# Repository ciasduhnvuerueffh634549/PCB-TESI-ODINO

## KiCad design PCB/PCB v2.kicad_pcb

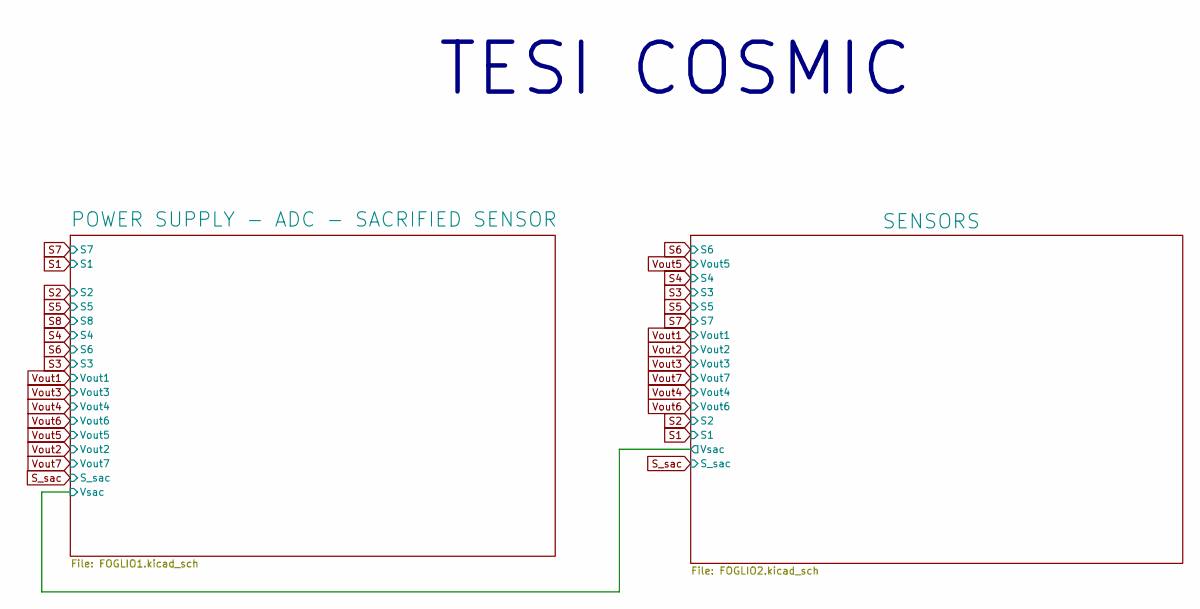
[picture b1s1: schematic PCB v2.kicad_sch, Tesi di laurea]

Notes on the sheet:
TESI COSMIC

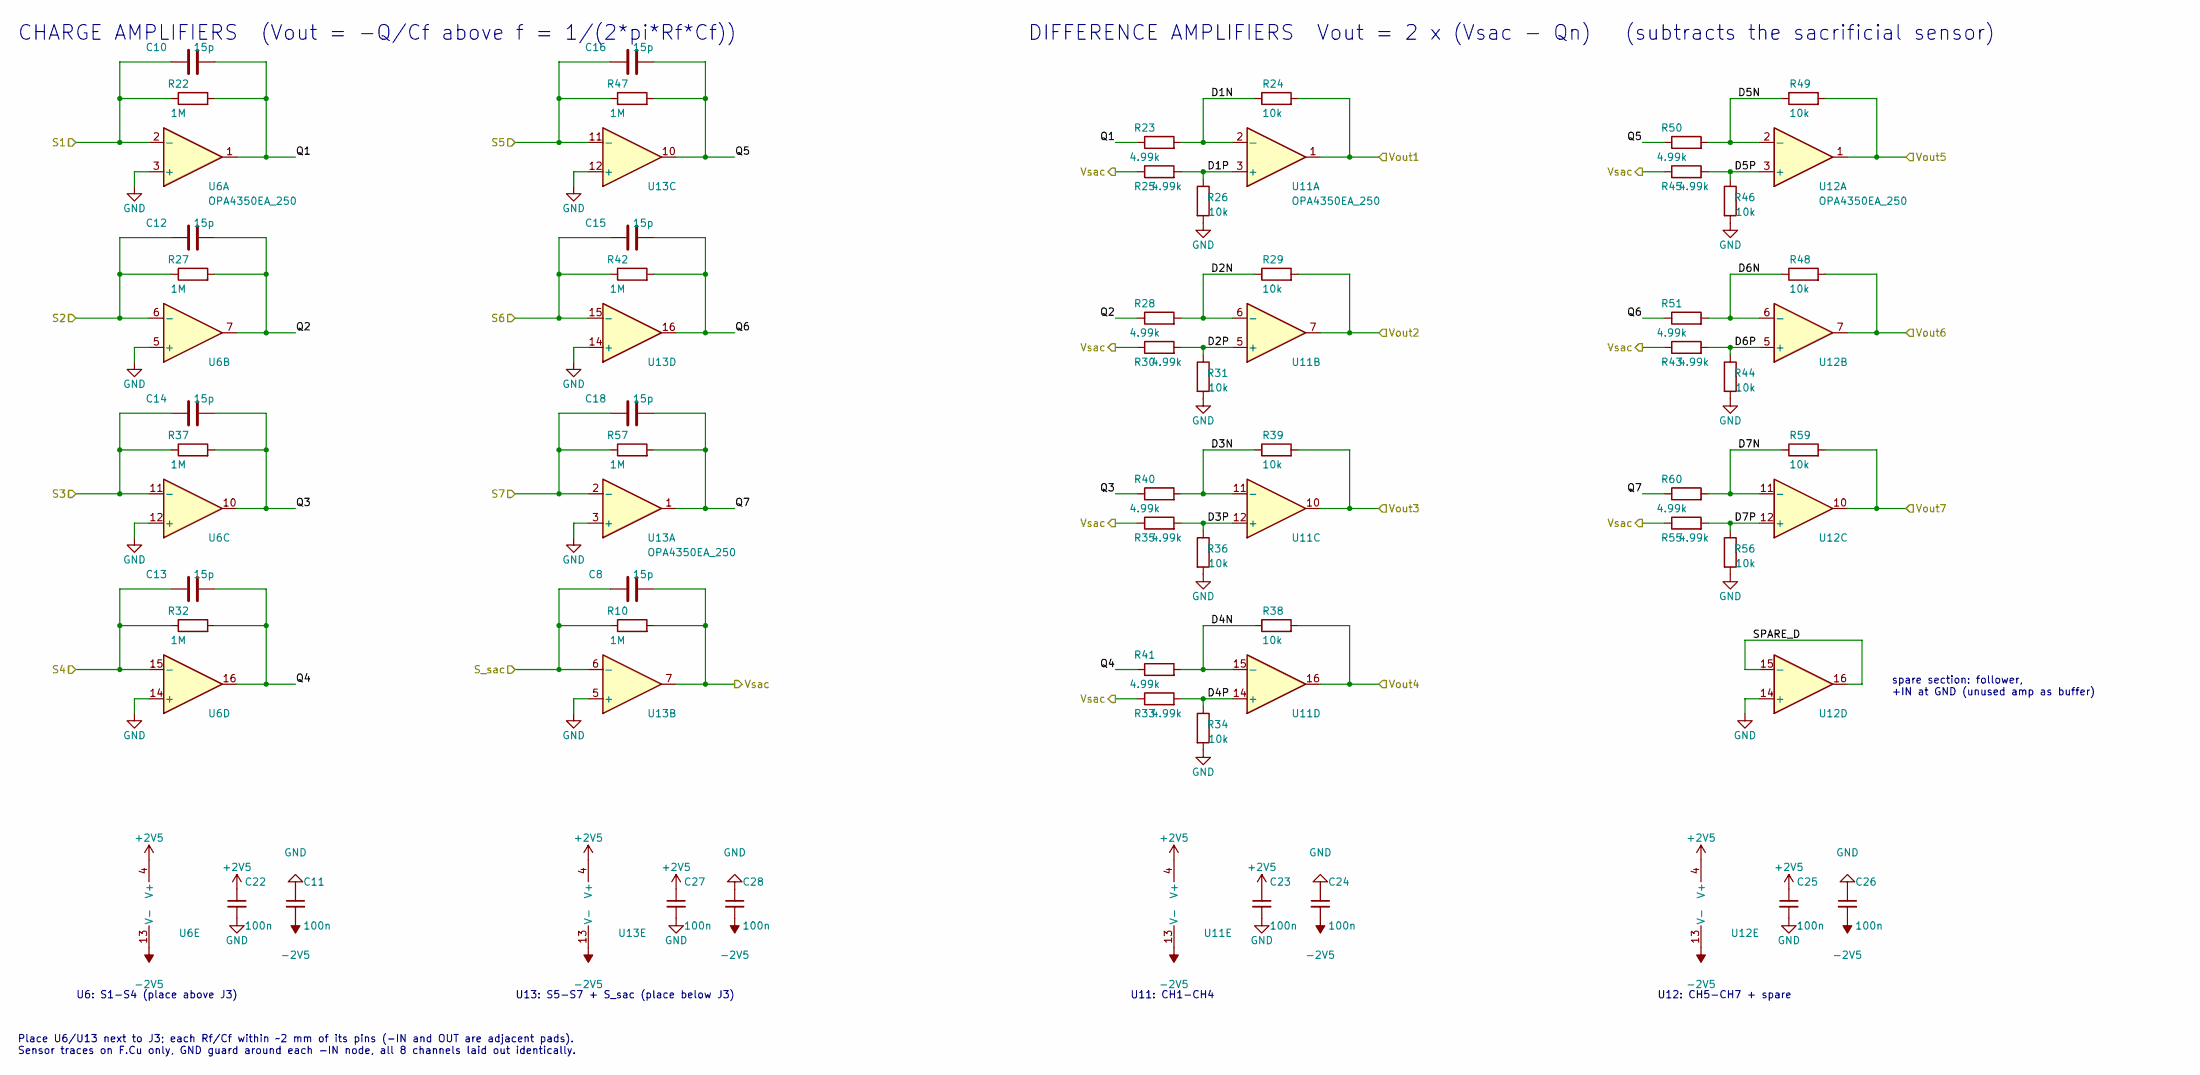
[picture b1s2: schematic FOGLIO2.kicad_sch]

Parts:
C8, C10, C12, C13, C14, C15, C16, C18: 15p; C_0603_1608Metric; MPN CL10C150JB8NNNC
C11, C22, C23, C24, C25, C26, C27, C28: 100n; C_0603_1608Metric; MPN GRM188R72A104KA35D
R10, R22, R27, R32, R37, R42, R47, R57: 1M; R_0603_1608Metric; MPN RN73R1JTTD1004B25
R23, R25, R28, R30, R33, R35, R40, R41, R43, R45, R50, R51, R55, R60: 4.99k; R_0603_1608Metric; MPN RT0603BRD074K99L
R24, R26, R29, R31, R34, R36, R38, R39, R44, R46, R48, R49, R56, R59: 10k; R_0603_1608Metric; MPN RT0603BRD0710KL
U6, U11, U12, U13: OPA4350EA_250; SOP63P600X175-16N; MPN OPA4350EA/250

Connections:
+2V5: C22.1, C23.1, C25.1, C27.1, U6.4 (V+), U11.4 (V+), U12.4 (V+), U13.4 (V+); also elsewhere on the board
-2V5: C11.2, C24.2, C26.2, C28.2, U6.13 (V-), U11.13 (V-), U12.13 (V-), U13.13 (V-); also elsewhere on the board
/POWER SUPPLY - ADC - SACRIFIED SENSOR/Vsac: C8.2, R10.2, R25.1, R30.1, R33.1, R35.1, R43.1, R45.1, R55.1, U13.7; also elsewhere on the board
/SENSORS/D1N: R23.2, R24.1, U11.2 (-)
/SENSORS/D1P: R25.2, R26.1, U11.3 (+)
/SENSORS/D2N: R28.2, R29.1, U11.6 (-)
/SENSORS/D2P: R30.2, R31.1, U11.5 (+)
/SENSORS/D3N: R39.1, R40.2, U11.11 (-)
/SENSORS/D3P: R35.2, R36.1, U11.12 (+)
/SENSORS/D4N: R38.1, R41.2, U11.15 (-)
/SENSORS/D4P: R33.2, R34.1, U11.14 (+)
/SENSORS/D5N: R49.1, R50.2, U12.2 (-)
/SENSORS/D5P: R45.2, R46.1, U12.3 (+)
/SENSORS/D6N: R48.1, R51.2, U12.6 (-)
/SENSORS/D6P: R43.2, R44.1, U12.5 (+)
/SENSORS/D7N: R59.1, R60.2, U12.11 (-)
/SENSORS/D7P: R55.2, R56.1, U12.12 (+)
/SENSORS/Q1: C10.2, R22.2, R23.1, U6.1
/SENSORS/Q2: C12.2, R27.2, R28.1, U6.7
/SENSORS/Q3: C14.2, R37.2, R40.1, U6.10
/SENSORS/Q4: C13.2, R32.2, R41.1, U6.16
/SENSORS/Q5: C16.2, R47.2, R50.1, U13.10
/SENSORS/Q6: C15.2, R42.2, R51.1, U13.16
/SENSORS/Q7: C18.2, R57.2, R60.1, U13.1
/SENSORS/SPARE_D: U12.15 (-), U12.16
GND: C11.1, C22.2, C23.2, C24.1, C25.2, C26.1, C27.2, C28.1, R26.2, R31.2, R34.2, R36.2, R44.2, R46.2, R56.2, U6.3 (+), U6.5 (+), U6.12 (+), U6.14 (+), U12.14 (+), U13.3 (+), U13.5 (+), U13.12 (+), U13.14 (+); also elsewhere on the board
S1: C10.1, R22.1, U6.2 (-); also elsewhere on the board
S2: C12.1, R27.1, U6.6 (-); also elsewhere on the board
S3: C14.1, R37.1, U6.11 (-); also elsewhere on the board
S4: C13.1, R32.1, U6.15 (-); also elsewhere on the board
S5: C16.1, R47.1, U13.11 (-); also elsewhere on the board
S6: C15.1, R42.1, U13.15 (-); also elsewhere on the board
S7: C18.1, R57.1, U13.2 (-); also elsewhere on the board
S_sac: C8.1, R10.1, U13.6 (-); also elsewhere on the board
Vout1: R24.2, U11.1; also elsewhere on the board
Vout2: R29.2, U11.7; also elsewhere on the board
Vout3: R39.2, U11.10; also elsewhere on the board
Vout4: R38.2, U11.16; also elsewhere on the board
Vout5: R49.2, U12.1; also elsewhere on the board
Vout6: R48.2, U12.7; also elsewhere on the board
Vout7: R59.2, U12.10; also elsewhere on the board

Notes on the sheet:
Place U6/U13 next to J3; each Rf/Cf within ~2 mm of its pins (-IN and OUT are adjacent pads). Sensor traces on F.Cu only, GND guard around each -IN node, all 8 channels laid out identically.
U12: CH5-CH7 + spare
U13: S5-S7 + S_sac (place below J3)
CHARGE AMPLIFIERS (Vout = -Q/Cf above f = 1/(2*pi*Rf*Cf))
spare section: follower, +IN at GND (unused amp as buffer)
U6: S1-S4 (place above J3)
U11: CH1-CH4
DIFFERENCE AMPLIFIERS Vout = 2 x (Vsac - Qn) (subtracts the sacrificial sensor)

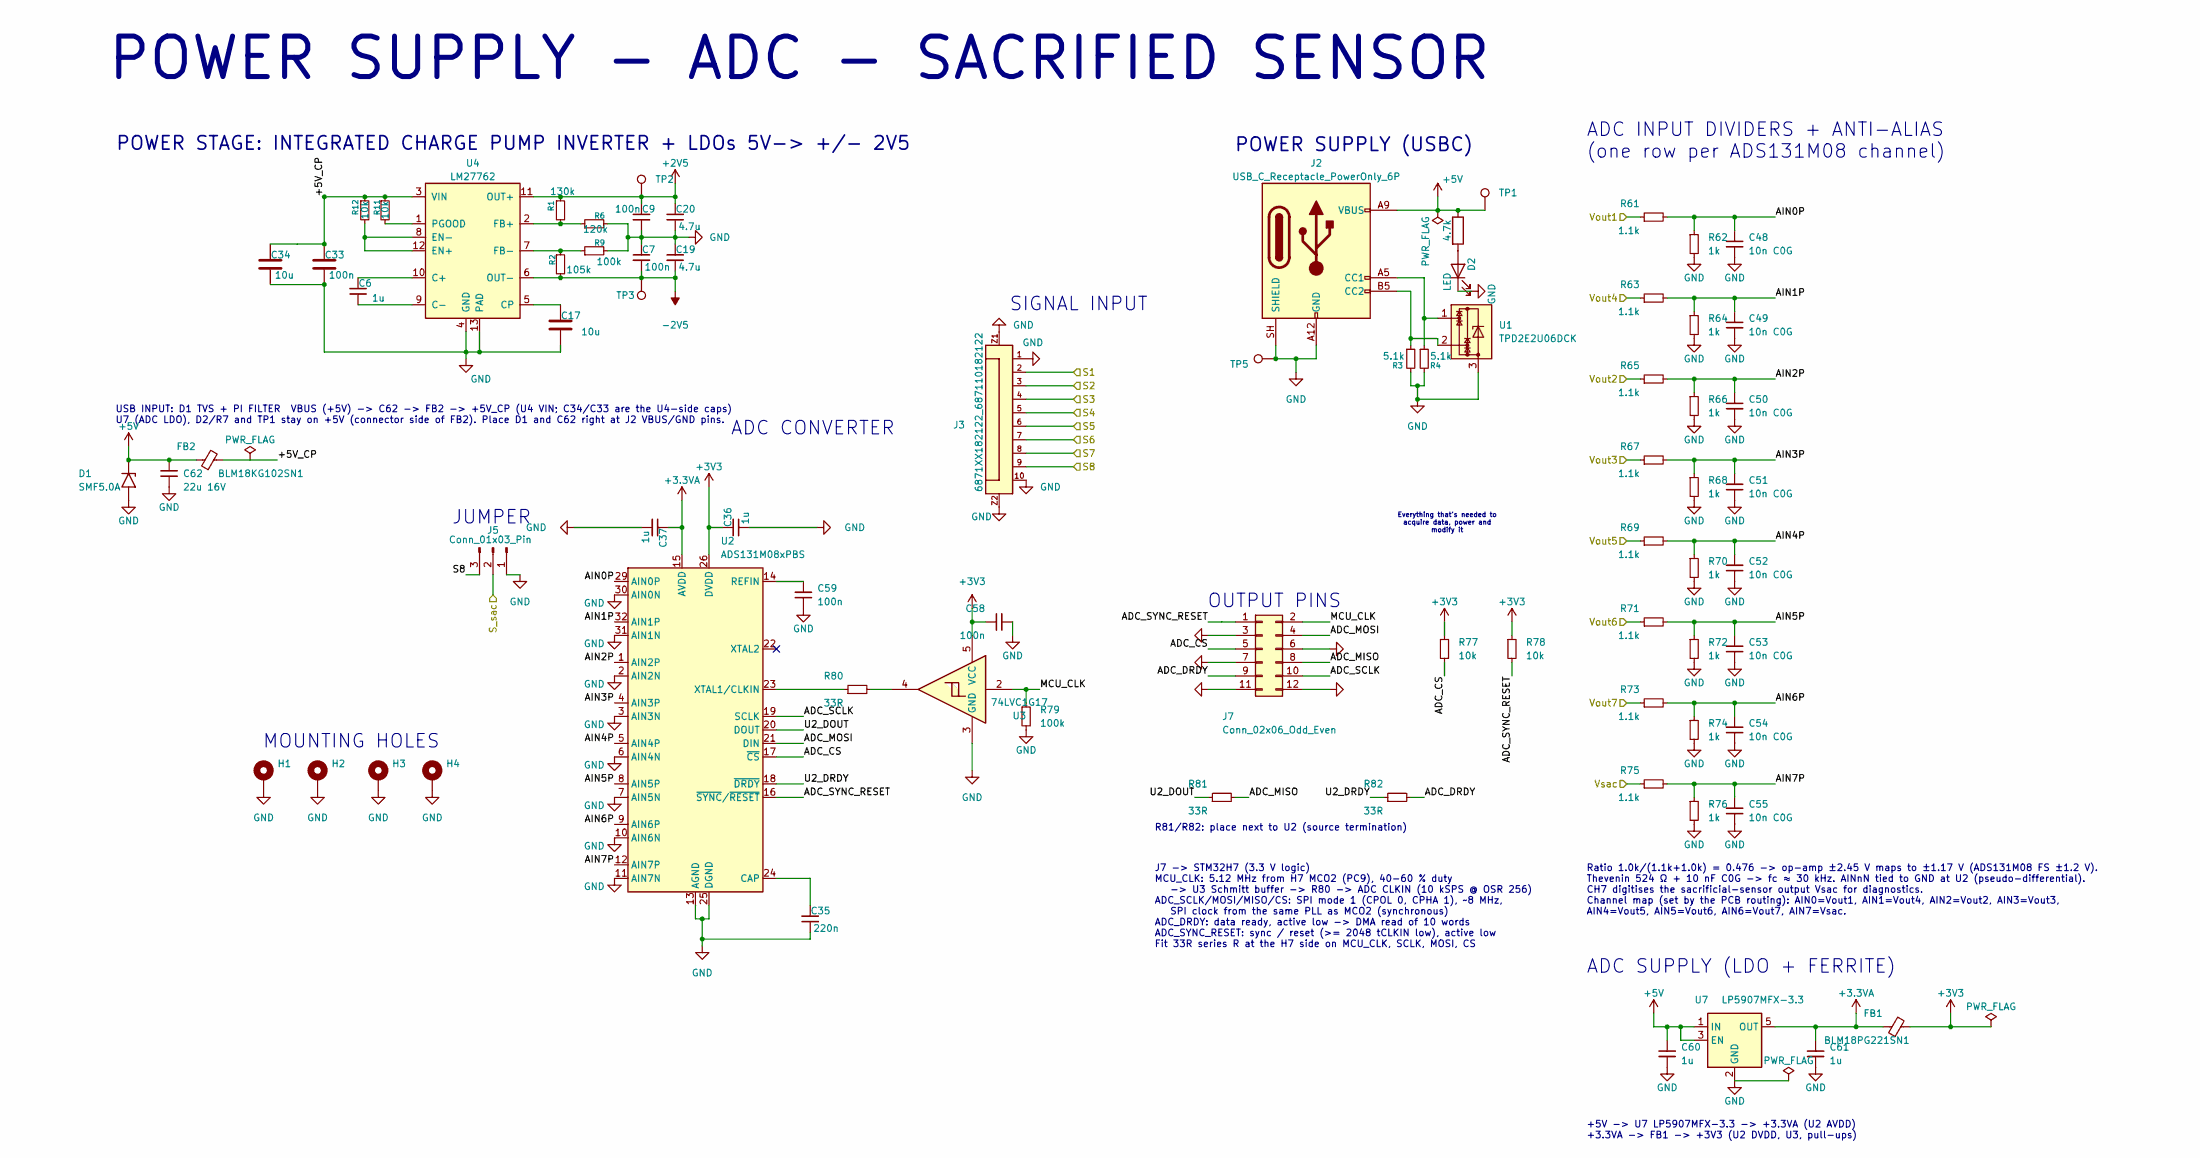
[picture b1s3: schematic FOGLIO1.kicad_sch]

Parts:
C6, C36, C37, C60, C61: 1u; C_0603_1608Metric; MPN GRT188R71E105KE13D
C7, C9, C33, C58, C59: 100n; C_0603_1608Metric; MPN GRM188R72A104KA35D
C17, C34: 10u; C_0805_2012Metric; MPN GRJ21BR61E106KE01L
C19, C20: 4.7u; C_0603_1608Metric; MPN GRT188R61C475KE13D
C35: 220n; C_0603_1608Metric; MPN GRM188R71E224KA88D
C48, C49, C50, C51, C52, C53, C54, C55: 10n C0G; C_0603_1608Metric; MPN GRM1885C1H103JA01D
C62: 22u 16V; C_0805_2012Metric; MPN GRM219R61C226ME15K
D1: SMF5.0A; D_SMF; MPN SMF5.0A
D2: LED; LED_0603_1608Metric; MPN 150060GS75000
FB1: BLM18PG221SN1; L_0603_1608Metric; MPN BLM18PG221SN1D
FB2: BLM18KG102SN1; L_0603_1608Metric; MPN BLM18KG102SN1D
H1, H2, H3, H4: MountingHole_Pad; MountingHole_2.2mm_M2_DIN965_Pad
J2: USB_C_Receptacle_PowerOnly_6P; USB_C_Receptacle_GCT_USB4125-xx-x_6P_TopMnt_Horizontal; MPN USB4125-GF-A
J3: 6871XX182122_687110182122; 687110182122; MPN 687110182122
J5: Conn_01x03_Pin; PinHeader_1x03_P1.27mm_Vertical_SMD_Pin1Right; MPN M50-3630342
J7: Conn_02x06_Odd_Even; PinHeader_2x06_P2.54mm_Vertical_SMD; MPN 61001221121
R1: 130k; R_0603_1608Metric; MPN RC0603FR-07130KL
R2: 105k; R_0603_1608Metric; MPN AC0603FR-07105KL
R3, R4: 5.1k; R_0603_1608Metric; MPN RC0603FR-075K1L
R6: 120k; R_0603_1608Metric; MPN RC0603FR-07120KL
R7: 4.7k; R_0603_1608Metric; MPN RC0603FR-074K7L
R9, R79: 100k; R_0603_1608Metric; MPN RC0603FR-07100KL
R11, R12, R77, R78: 10k; R_0603_1608Metric; MPN RC0603FR-0710KL
R61, R63, R65, R67, R69, R71, R73, R75: 1.1k; R_0603_1608Metric; MPN RT0603BRD071K1L
R62, R64, R66, R68, R70, R72, R74, R76: 1k; R_0603_1608Metric; MPN RN73R1JTTD1001B25
R80, R81, R82: 33R; R_0603_1608Metric; MPN RC0603FR-0733RL
TP1, TP2, TP3, TP5: TestPoint; TestPoint_Pad_D1.5mm
U1: TPD2E2U06DCK; SOT-323_SC-70; MPN TPD2E2U06DCKR
U2: ADS131M08xPBS; TQFP-32_5x5mm_P0.5mm; MPN ADS131M08IPBSR
U3: 74LVC1G17; SOT-23-5; MPN SN74LVC1G17DBVR
U4: LM27762; WSON-12-1EP_3x2mm_P0.5mm_EP1x2.65_ThermalVias; MPN LM27762DSSR
U7: LP5907MFX-3.3; SOT-23-5; MPN LP5907MFX-3.3/NOPB

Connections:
+2V5: C9.1, C20.1, R1.1, TP2.1 (1_1), U4.11 (OUT+); also elsewhere on the board
+3.3VA: C37.1, C61.1, FB1.1, U2.15 (AVDD), U7.5 (OUT)
+3V3: C36.1, C58.1, FB1.2, R77.1, R78.1, U2.26 (DVDD), U3.5 (VCC)
+5V: C60.1, C62.1, D1.1 (A1), FB2.1, J2.A9 (VBUS), J2.B9 (VBUS), R7.1, TP1.1 (1_1), U7.1 (IN), U7.3 (EN)
-2V5: C7.2, C19.2, R2.2, TP3.1 (1_1), U4.6 (OUT-); also elsewhere on the board
/POWER SUPPLY - ADC - SACRIFIED SENSOR/+5V_CP: C33.1, C34.1, FB2.2, R11.1, R12.1, U4.3 (VIN)
/POWER SUPPLY - ADC - SACRIFIED SENSOR/ADC_CS: J7.5, R77.2, U2.17 (~CS)
/POWER SUPPLY - ADC - SACRIFIED SENSOR/ADC_DRDY: J7.9, R82.2
/POWER SUPPLY - ADC - SACRIFIED SENSOR/ADC_MISO: J7.8, R81.2
/POWER SUPPLY - ADC - SACRIFIED SENSOR/ADC_MOSI: J7.4, U2.21 (DIN)
/POWER SUPPLY - ADC - SACRIFIED SENSOR/ADC_SCLK: J7.10, U2.19 (SCLK)
/POWER SUPPLY - ADC - SACRIFIED SENSOR/ADC_SYNC_RESET: J7.1, R78.2, U2.16 (~SYNC/~RESET)
/POWER SUPPLY - ADC - SACRIFIED SENSOR/AIN0P: C48.1, R61.2, R62.1, U2.29 (AIN0P)
/POWER SUPPLY - ADC - SACRIFIED SENSOR/AIN1P: C49.1, R63.2, R64.1, U2.32 (AIN1P)
/POWER SUPPLY - ADC - SACRIFIED SENSOR/AIN2P: C50.1, R65.2, R66.1, U2.1 (AIN2P)
/POWER SUPPLY - ADC - SACRIFIED SENSOR/AIN3P: C51.1, R67.2, R68.1, U2.4 (AIN3P)
/POWER SUPPLY - ADC - SACRIFIED SENSOR/AIN4P: C52.1, R69.2, R70.1, U2.5 (AIN4P)
/POWER SUPPLY - ADC - SACRIFIED SENSOR/AIN5P: C53.1, R71.2, R72.1, U2.8 (AIN5P)
/POWER SUPPLY - ADC - SACRIFIED SENSOR/AIN6P: C54.1, R73.2, R74.1, U2.9 (AIN6P)
/POWER SUPPLY - ADC - SACRIFIED SENSOR/AIN7P: C55.1, R75.2, R76.1, U2.12 (AIN7P)
/POWER SUPPLY - ADC - SACRIFIED SENSOR/MCU_CLK: J7.2, R79.1, U3.2
/POWER SUPPLY - ADC - SACRIFIED SENSOR/U2_DOUT: R81.1, U2.20 (DOUT)
/POWER SUPPLY - ADC - SACRIFIED SENSOR/U2_DRDY: R82.1, U2.18 (~DRDY)
/POWER SUPPLY - ADC - SACRIFIED SENSOR/Vsac: R75.1; also elsewhere on the board
GND: C7.1, C9.2, C17.2, C19.1, C20.2, C33.2, C34.2, C35.2, C36.2, C37.2, C48.2, C49.2, C50.2, C51.2, C52.2, C53.2, C54.2, C55.2, C58.2, C59.2, C60.2, C61.2, C62.2, D1.2 (A2), D2.1 (K), H1.1 (1_1), H2.1 (1_1), H3.1 (1_1), H4.1 (1_1), J2.A12 (GND), J2.B12 (GND), J2.SH (SHIELD), J3.1, J3.10, J3.Z1, J3.Z2, J5.1, J7.3, J7.6, J7.7, J7.11, J7.12, R3.2, R4.2, R6.2, R9.2, R62.2, R64.2, R66.2, R68.2, R70.2, R72.2, R74.2, R76.2, R79.2, TP5.1 (1_1), U1.3, U2.2 (AIN2N), U2.3 (AIN3N), U2.6 (AIN4N), U2.7 (AIN5N), U2.10 (AIN6N), U2.11 (AIN7N), U2.13 (AGND), U2.25 (DGND), U2.27 (AGND), U2.28 (AGND), U2.30 (AIN0N), U2.31 (AIN1N), U3.3 (GND), U4.4 (GND), U4.13 (PAD), U7.2 (GND); also elsewhere on the board
unnamed: D2.2 (A), R7.2
unnamed: J2.A5 (CC1), R4.1, U1.1
unnamed: J2.B5 (CC2), R3.1, U1.2
unnamed: R80.2, U3.4
unnamed: C35.1, U2.24 (CAP)
unnamed: C59.1, U2.14 (REFIN)
unnamed: R80.1, U2.23 (XTAL1/CLKIN)
unnamed: C6.1, U4.10 (C+)
unnamed: C6.2, U4.9 (C-)
unnamed: C17.1, U4.5 (CP)
unnamed: R12.2, U4.8 (EN-), U4.12 (EN+)
unnamed: R1.2, R6.1, U4.2 (FB+)
unnamed: R2.1, R9.1, U4.7 (FB-)
unnamed: R11.2, U4.1 (PGOOD)
S1: J3.2; also elsewhere on the board
S2: J3.3; also elsewhere on the board
S3: J3.4; also elsewhere on the board
S4: J3.5; also elsewhere on the board
S5: J3.6; also elsewhere on the board
S6: J3.7; also elsewhere on the board
S7: J3.8; also elsewhere on the board
S8: J3.9, J5.3
S_sac: J5.2; also elsewhere on the board
Vout1: R61.1; also elsewhere on the board
Vout2: R65.1; also elsewhere on the board
Vout3: R67.1; also elsewhere on the board
Vout4: R63.1; also elsewhere on the board
Vout5: R69.1; also elsewhere on the board
Vout6: R71.1; also elsewhere on the board
Vout7: R73.1; also elsewhere on the board

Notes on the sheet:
SIGNAL INPUT
MOUNTING HOLES
POWER STAGE: INTEGRATED CHARGE PUMP INVERTER + LDOs 5V-> +/- 2V5
ADC INPUT DIVIDERS + ANTI-ALIAS (one row per ADS131M08 channel)
ADC CONVERTER
ADC SUPPLY (LDO + FERRITE)
J7 -> STM32H7 (3.3 V logic) MCU_CLK: 5.12 MHz from H7 MCO2 (PC9), 40-60 % duty -> U3 Schmitt buffer -> R80 -> ADC CLKIN (10 kSPS @ OSR 256) ADC_SCLK/MOSI/MISO/CS: SPI mode 1 (CPOL 0, CPHA 1), ~8 MHz, SPI clock from the same PLL as MCO2 (synchronous) ADC_DRDY: data ready, active low -> DMA read of 1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
R81/R82: place next to U2 (source termination)
Ratio 1.0k/(1.1k+1.0k) = 0.476 -> op-amp ±2.45 V maps to ±1.17 V (ADS131M08 FS ±1.2 V). Thevenin 524 Ω + 10 nF C0G -> fc ≈ 30 kHz. AINnN tied to GND at U2 (pseudo-differential). CH7 digitises the sacrificial-sensor output Vsac for diagnostics. Channel map (set by the PCB routing): AIN0=Vout1, AIN1=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
Everything that's needed to acquire data, power and modify it
POWER SUPPLY (USBC)
POWER SUPPLY - ADC - SACRIFIED SENSOR
OUTPUT PINS
JUMPER
+5V -> U7 LP5907MFX-3.3 -> +3.3VA (U2 AVDD) +3.3VA -> FB1 -> +3V3 (U2 DVDD, U3, pull-ups)
USB INPUT: D1 TVS + PI FILTER VBUS (+5V) -> C62 -> FB2 -> +5V_CP (U4 VIN; C34/C33 are the U4-side caps) U7 (ADC LDO), D2/R7 and TP1 stay on +5V (connector side of FB2). Place D1 and C62 right at J2 VBUS/GND pins.

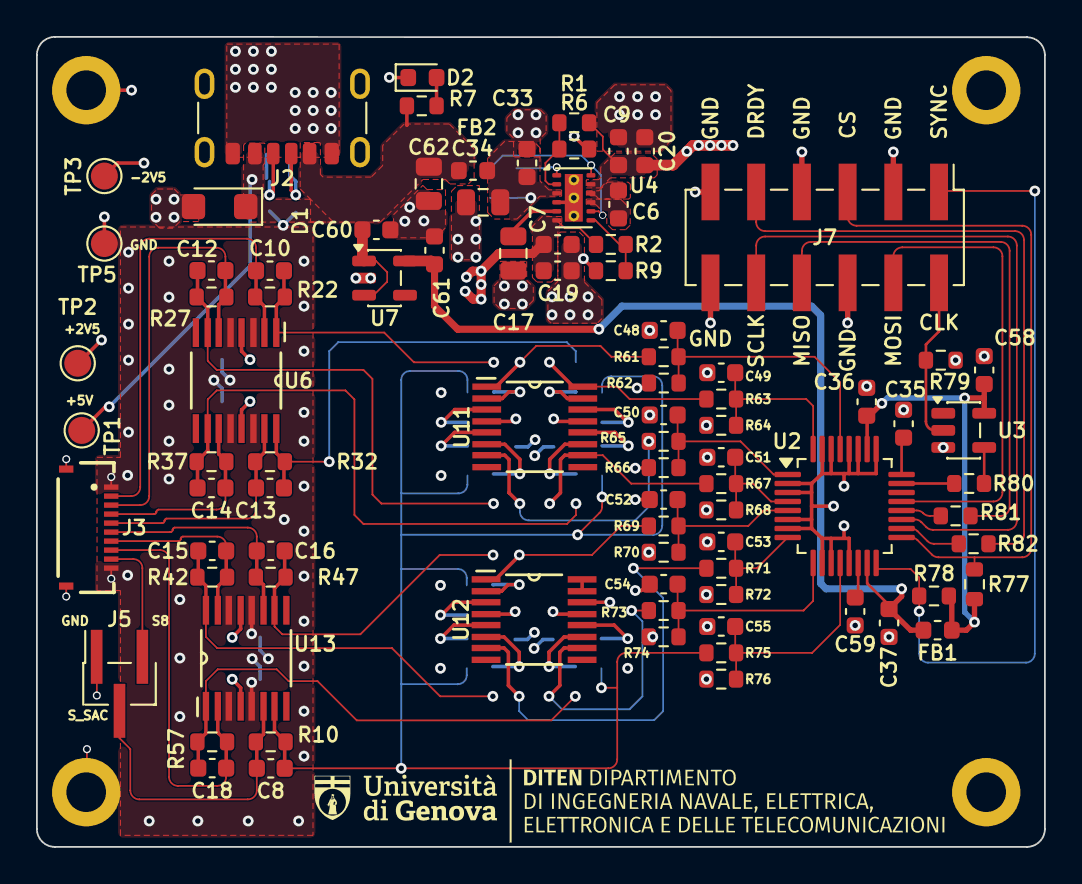
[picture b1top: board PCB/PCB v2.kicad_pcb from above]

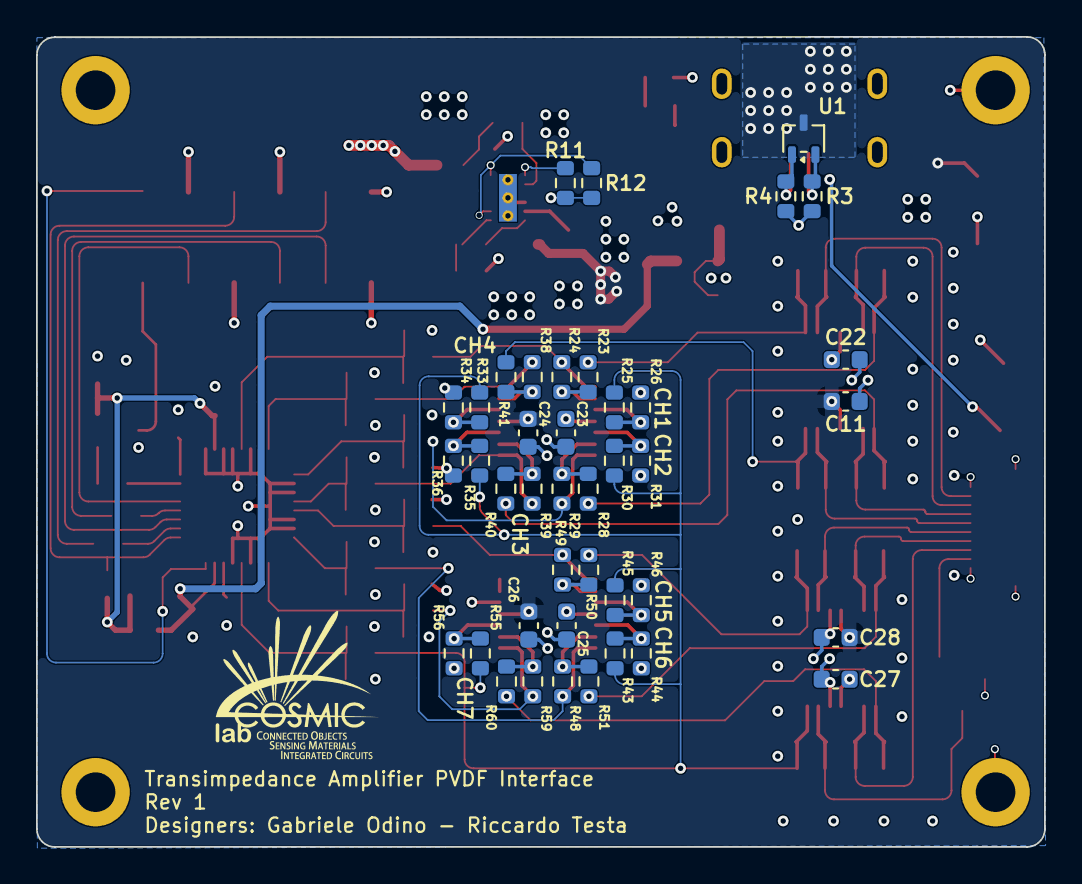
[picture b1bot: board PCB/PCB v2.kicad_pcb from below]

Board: 4 copper layers, 56.0 x 45.0 mm, 132 parts (41 on the bottom side), 77 nets.

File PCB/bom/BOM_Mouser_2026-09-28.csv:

Qty per board,References,Value,Description,Manufacturer,MPN,Mouser link,Mouser stock (2026-09-28),EUR/pc @10,EUR/pc @100,Footprint,Notes
5,"C6,C36,C37,C60,C61",1u,1 µF 25V X7R 0603,Murata,GRT188R71E105KE13D,https://www.mouser.it/c/?q=GRT188R71E105KE13D,"140,413",0.046,0.040,Capacitor_SMD:C_0603_1608Metric,
13,"C7,C9,C11,C22,C23,C24,C25,C26,C27,C28,C33,C58,C59",100n,100 nF 100V X7R 0603,Murata,GRM188R72A104KA35D,https://www.mouser.it/c/?q=GRM188R72A104KA35D,"1,304,093",0.075,0.046,Capacitor_SMD:C_0603_1608Metric,Replaces obsolete GRM188R71H104KA93D
8,"C8,C10,C12,C13,C14,C15,C16,C18",15p,15 pF 50V C0G ±5% 0603,Samsung Electro-Mechanics,CL10C150JB8NNNC,https://www.mouser.it/c/?q=CL10C150JB8NNNC,"53,656",0.039,0.023,Capacitor_SMD:C_0603_1608Metric,Rf||Cf; Murata 0603 15p C0G all NRND
2,"C17,C34",10u,10 µF 25V X5R 0805 soft term.,Murata,GRJ21BR61E106KE01L,https://www.mouser.it/c/?q=GRJ21BR61E106KE01L,"21,004",0.064,0.056,Capacitor_SMD:C_0805_2012Metric,C17 at about -5V; check DC bias
2,"C19,C20",4.7u,4.7 µF 16V X5R 0603,Murata,GRT188R61C475KE13D,https://www.mouser.it/c/?q=GRT188R61C475KE13D,"7,003",0.068,0.059,Capacitor_SMD:C_0603_1608Metric,±2V5 LDO outputs; check DC bias
1,C35,220n,220 nF 25V X7R 0603,Murata,GRM188R71E224KA88D,https://www.mouser.it/c/?q=GRM188R71E224KA88D,"9,632",0.043,0.026,Capacitor_SMD:C_0603_1608Metric,ADC CAP pin
8,"C48,C49,C50,C51,C52,C53,C54,C55",10n C0G,10 nF 50V C0G ±5% 0603,Murata,GRM1885C1H103JA01D,https://www.mouser.it/c/?q=GRM1885C1H103JA01D,"225,876",0.061,0.037,Capacitor_SMD:C_0603_1608Metric,ADC anti-alias
1,C62,22u 16V,22 µF 16V X5R 0805,Murata,GRM219R61C226ME15K,https://www.mouser.it/c/?q=GRM219R61C226ME15K,"24,889",0.170,0.111,Capacitor_SMD:C_0805_2012Metric,USB input C of the pi filter
1,D1,SMF5.0A,TVS 5V unidirectional 200W SOD-123FL,Littelfuse,SMF5.0A,https://www.mouser.it/c/?q=SMF5.0A,"1,815",0.231,0.152,Diode_SMD:D_SMF,Pick the Littelfuse listing
1,D2,LED,LED green 0603,Würth Elektronik,150060GS75000,https://www.mouser.it/c/?q=150060GS75000,not checked,,,LED_SMD:LED_0603_1608Metric,Power LED; verify stock
1,FB1,BLM18PG221SN1,Ferrite bead 220Ω@100MHz 0603,Murata,BLM18PG221SN1D,https://www.mouser.it/c/?q=BLM18PG221SN1D,"122,451",0.053,0.035,Inductor_SMD:L_0603_1608Metric,
1,FB2,BLM18KG102SN1,Ferrite bead 1000Ω@100MHz 1A 0603,Murata,BLM18KG102SN1D,https://www.mouser.it/c/?q=BLM18KG102SN1D,"122,995",0.055,0.039,Inductor_SMD:L_0603_1608Metric,Pi filter
1,J2,USB_C_Receptacle_PowerOnly_6P,"USB-C receptacle, power only 6P",GCT,USB4125-GF-A,https://www.mouser.it/c/?q=USB4125-GF-A,not checked,,,Connector_USB:USB_C_Receptacle_GCT_USB4125-xx-x_6P_TopMnt_Horizontal,Verify stock
1,J3,6871XX182122_687110182122,FFC/FPC connector 10p 0.5mm,Würth Elektronik,687110182122,https://www.mouser.it/c/?q=687110182122,not checked,,,CONNETTORE 687110182122:687110182122,Sensor input; verify stock
1,J5,Conn_01x03_Pin,"Pin header 1x03 1.27 mm vertical SMD, alternating tails (Archer M50)",Harwin,M50-3630342,https://www.mouser.it/ProductDetail/Harwin/M50-3630342,not verified,not verified,not verified,Connector_PinHeader_1.27mm:PinHeader_1x03_P1.27mm_Vertical_SMD_Pin1Right,"Mouser 855-M50-3630342. Datasheet land pattern (0.65x3.0 mm pads, 6.0 mm span) matches the footprint. Aggregator ~$0.32/pc @10; Farnell 3226059 EUR 0.241 @10. Recheck Mouser stock/price. NOT M50-3530342 (through-hole)."
1,(J5 jumper),Shunt 1.27 mm,"Jumper socket 2-way 1.27 mm with handle, black (fits 0.4 mm sq posts)",Harwin,M50-2000005,https://www.mouser.it/ProductDetail/Harwin/M50-2000005,not verified,not verified,not verified,(not a PCB part),Mouser 855-M50-2000005. Mates with M50-3630342. Aggregator ~$0.31/pc @10; Farnell 2078263 EUR 0.236 @10. Red: M50-2020005. Recheck Mouser stock/price.
1,J7,Conn_02x06_Odd_Even,Pin header 2x06 2.54mm SMT,Würth Elektronik,61001221121,https://www.mouser.it/c/?q=61001221121,not checked,,,Connector_PinHeader_2.54mm:PinHeader_2x06_P2.54mm_Vertical_SMD,Check land pattern vs KiCad SMD footprint
1,R1,130k,130 kΩ 1% thick film 0603,Yageo,RC0603FR-07130KL,https://www.mouser.it/c/?q=RC0603FR-07130KL,in stock,0.012,0.007,PCM_SparkFun-Resistor:R_0603_1608Metric,
1,R2,105k,105 kΩ 1% thick film 0603,Yageo,AC0603FR-07105KL,https://www.mouser.it/c/?q=AC0603FR-07105KL,"39,037",0.015,0.010,PCM_SparkFun-Resistor:R_0603_1608Metric,RC0603FR-07105KL out of stock
2,"R3,R4",5.1k,5.1 kΩ 1% thick film 0603,Yageo,RC0603FR-075K1L,https://www.mouser.it/c/?q=RC0603FR-075K1L,in stock,0.015,0.009,PCM_SparkFun-Resistor:R_0603_1608Metric,USB-C CC pull-downs
1,R6,120k,120 kΩ 1% thick film 0603,Yageo,RC0603FR-07120KL,https://www.mouser.it/c/?q=RC0603FR-07120KL,in stock,0.012,0.007,PCM_SparkFun-Resistor:R_0603_1608Metric,
1,R7,4.7k,4.7 kΩ 1% thick film 0603,Yageo,RC0603FR-074K7L,https://www.mouser.it/c/?q=RC0603FR-074K7L,in stock,0.012,0.007,Resistor_SMD:R_0603_1608Metric,
2,"R9,R79",100k,100 kΩ 1% thick film 0603,Yageo,RC0603FR-07100KL,https://www.mouser.it/c/?q=RC0603FR-07100KL,"5,040,000",0.012,0.007,PCM_SparkFun-Resistor:R_0603_1608Metric,
8,"R10,R22,R27,R32,R37,R42,R47,R57",1M,1 MΩ 0.1% 25ppm thin film 0603,KOA Speer,RN73R1JTTD1004B25,https://www.mouser.it/c/?q=RN73R1JTTD1004B25,"2,483",0.066,0.063,Resistor_SMD:R_0603_1608Metric,Transimpedance Rf
4,"R11,R12,R77,R78",10k,10 kΩ 1% thick film 0603,Yageo,RC0603FR-0710KL,https://www.mouser.it/c/?q=RC0603FR-0710KL,in stock,0.012,0.007,PCM_SparkFun-Resistor:R_0603_1608Metric,
14,"R23,R25,R28,R30,R33,R35,R40,R41,R43,R45,R50,R51,R55,R60",4.99k,4.99 kΩ 0.1% 25ppm thin film 0603,Yageo,RT0603BRD074K99L,https://www.mouser.it/c/?q=RT0603BRD074K99L,"49,304",0.052,0.048,Resistor_SMD:R_0603_1608Metric,Diff amp (was 5k)
14,"R24,R26,R29,R31,R34,R36,R38,R39,R44,R46,R48,R49,R56,R59",10k,10 kΩ 0.1% 25ppm thin film 0603,Yageo,RT0603BRD0710KL,https://www.mouser.it/c/?q=RT0603BRD0710KL,"146,030",0.052,0.048,Resistor_SMD:R_0603_1608Metric,Diff amp
8,"R61,R63,R65,R67,R69,R71,R73,R75",1.1k,1.1 kΩ 0.1% 25ppm thin film 0603,Yageo,RT0603BRD071K1L,https://www.mouser.it/c/?q=RT0603BRD071K1L,"22,217",0.052,0.048,Resistor_SMD:R_0603_1608Metric,ADC divider top
8,"R62,R64,R66,R68,R70,R72,R74,R76",1k,1 kΩ 0.1% 25ppm thin film 0603,KOA Speer,RN73R1JTTD1001B25,https://www.mouser.it/c/?q=RN73R1JTTD1001B25,"19,896",0.064,0.061,Resistor_SMD:R_0603_1608Metric,ADC divider bottom
3,"R80,R81,R82",33R,33 Ω 1% thick film 0603,Yageo,RC0603FR-0733RL,https://www.mouser.it/c/?q=RC0603FR-0733RL,in stock,0.012,0.007,Resistor_SMD:R_0603_1608Metric,Source terminations
1,U1,TPD2E2U06DCK,ESD protection 2-ch SC-70,Texas Instruments,TPD2E2U06DCKR,https://www.mouser.it/c/?q=TPD2E2U06DCKR,not checked,,,Package_TO_SOT_SMD:SOT-323_SC-70,Verify stock
1,U2,ADS131M08xPBS,"ADC 8-ch 24-bit simultaneous, TQFP-32",Texas Instruments,ADS131M08IPBSR,https://www.mouser.it/c/?q=ADS131M08IPBSR,"3,949",7.23,6.17,Package_QFP:TQFP-32_5x5mm_P0.5mm,
1,U3,74LVC1G17,Schmitt buffer SOT-23-5,Texas Instruments,SN74LVC1G17DBVR,https://www.mouser.it/c/?q=SN74LVC1G17DBVR,"24,151",0.087,0.065,Package_TO_SOT_SMD:SOT-23-5,
1,U4,LM27762,Inverting charge pump + ±LDOs WSON-12,Texas Instruments,LM27762DSSR,https://www.mouser.it/c/?q=LM27762DSSR,"19,005",1.38,1.14,Package_SON:WSON-12-1EP_3x2mm_P0.5mm_EP1x2.65_ThermalVias,
4,"U6,U11,U12,U13",OPA4350EA_250,Quad op-amp SSOP-16,Texas Instruments,OPA4350EA/250,https://www.mouser.it/c/?q=OPA4350EA/250,"1,050",8.53,7.31,Opa4:SOP63P600X175-16N,END OF LIFE (TI Last Time Buy): buy now
1,U7,LP5907MFX-3.3,LDO 3.3V 250mA low-noise SOT-23-5,Texas Instruments,LP5907MFX-3.3/NOPB,https://www.mouser.it/c/?q=LP5907MFX-3.3/NOPB,"114,650",0.399,0.312,Package_TO_SOT_SMD:SOT-23-5,Replaces TPS7A2033 (26 wk lead)

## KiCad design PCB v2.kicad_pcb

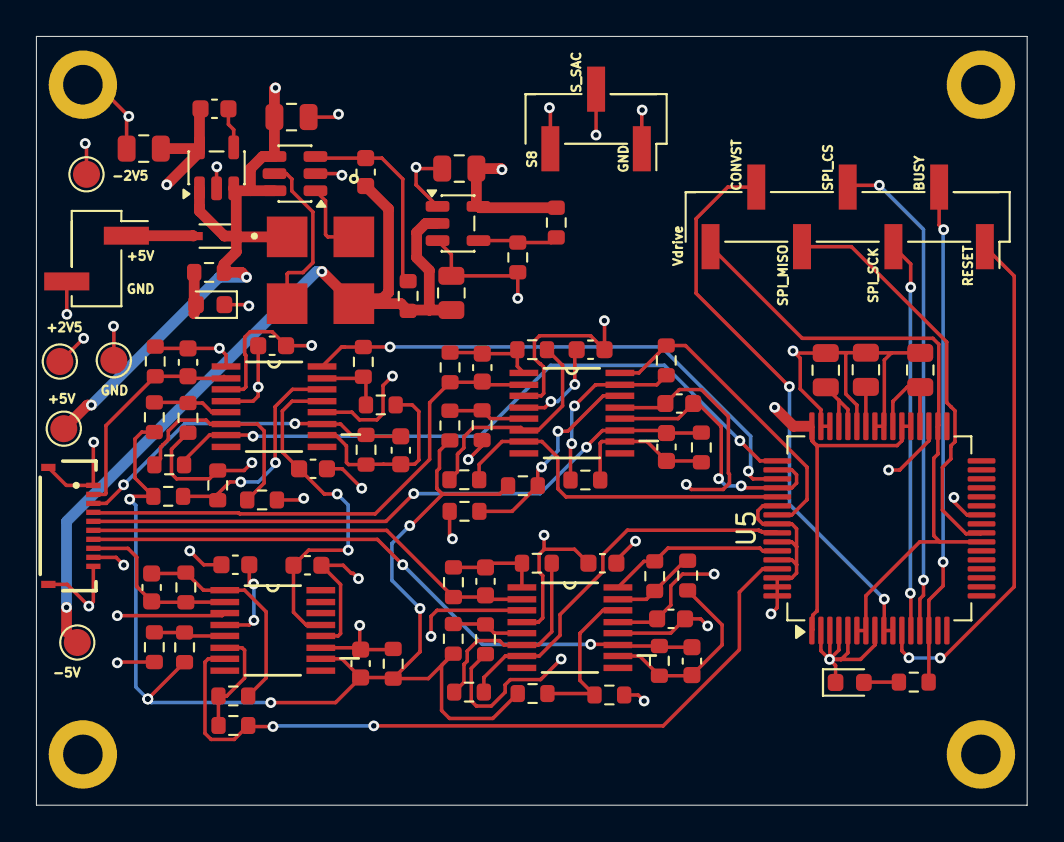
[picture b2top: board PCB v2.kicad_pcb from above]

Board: 4 copper layers, 55.0 x 42.7 mm, 91 parts (0 on the bottom side), 61 nets.

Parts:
C1: 4.7u; C_0805_2012Metric
C2: 22p; C_0603_1608Metric
C3, C4, C42, C46, C47: 10u; C_0805_2012Metric
C5: 0.01u; C_0603_1608Metric
C8, C10, C12, C13, C14, C15, C16, C18: 15p; C_0603_1608Metric
C11, C22, C23, C24, C25, C26, C27, C28: 100n; C_0603_1608Metric
C45: 1u; C_0805_2012Metric
D1: BAT760-7; SOD2513X120N
D2, D3: LED; LED_0603_1608Metric
H1, H2, H3, H4: MountingHole_Pad; MountingHole_2.2mm_M2_DIN965_Pad
J1: Conn_01x02_Pin; PinHeader_1x02_P2.54mm_Vertical_SMD_Pin1Right
J3: 6871XX182122_687110182122; 687110182122
J5: Conn_01x03_Pin; PinHeader_1x03_P2.54mm_Vertical_SMD_Pin1Right
J7: Conn_01x07_Pin; PinHeader_1x07_P2.54mm_Vertical_SMD_Pin1Right
L1: SDQ12-4R7-R; INDM5252X12N
R3: 511k; R_0603_1608Metric
R4: 105k; R_0603_1608Metric
R5: 100k; R_0603_1608Metric
R7, R8: 4.7k; R_0603_1608Metric
R10, R22, R27, R32, R37, R42, R47, R57: 1M; R_0603_1608Metric
R23, R25, R28, R30, R33, R35, R40, R41, R43, R45, R50, R51, R55, R60: 5k; R_0603_1608Metric
R24, R26, R29, R31, R34, R36, R38, R39, R44, R46, R48, R49, R56, R59: 10k; R_0603_1608Metric
TP1, TP2, TP3, TP4, TP5: TestPoint; TestPoint_Pad_D1.5mm
U1: LT3483AxS6; TSOT-23-6
U2: LT1761-2.5; TSOT-23-5
U3: LT1964-BYP; TSOT-23-5
U5: AD7606; LQFP-64_10x10mm_P0.5mm
U6, U11, U12, U13: OPA4350EA_250; SOP63P600X175-16N

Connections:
+2V5: C5.1, C22.1, C23.1, C25.1, C27.1, C42.1, TP2.1 (1_1), U2.5 (VOUT), U6.4 (+V), U11.4 (+V), U12.4 (+V), U13.4 (+V)
+5V: C1.1, D1.C, L1.2, R7.1, TP1.1 (1_1), U1.4 (~SHDN), U1.6 (V_{IN}), U2.1 (VIN), U2.3 (~SHDN), U5.1 (AVCC), U5.37 (AVCC), U5.38 (AVCC), U5.48 (AVCC)
-2V5: C4.2, C11.2, C24.2, C26.2, C28.2, R4.2, TP3.1 (1_1), U3.5 (VOUT), U6.13 (-V), U11.13 (-V), U12.13 (-V), U13.13 (-V)
-5V: C2.1, C3.1, L1.4, R3.1, TP4.1 (1_1), U3.2 (VIN)
BUSY: J7.2, R8.1, U5.14 (BUSY)
CONVST: J7.6, U5.9 (CONVST_A), U5.10 (CONVST_B)
GND: C1.2, C3.2, C4.1, C11.1, C22.2, C23.2, C24.1, C25.2, C26.1, C27.2, C28.1, C42.2, C45.2, C46.2, C47.2, D2.1 (K), D3.1 (K), H1.1 (1_1), H2.1 (1_1), H3.1 (1_1), H4.1 (1_1), J1.2, J3.1, J3.10, J3.Z1, J3.Z2, J5.1, R5.1, R26.1, R31.1, R34.1, R36.1, R44.1, R46.1, R56.1, TP5.1 (1_1), U1.2 (GND), U2.2 (GND), U3.1 (GND), U3.3 (BYP), U5.2 (AGND), U5.3 (OS0), U5.4 (OS1), U5.5 (OS2), U5.8 (RANGE), U5.26 (AGND), U5.35 (AGND), U5.40 (AGND), U5.41 (AGND), U5.43 (REFGND), U5.46 (REFGND), U5.47 (AGND), U5.50 (V1GND), U5.52 (V2GND), U5.54 (V3GND), U5.56 (V4GND), U5.58 (V5GND), U5.60 (V6GND), U5.62 (V7GND), U5.63 (V8), U5.64 (V8GND), U6.3 (+IN_A), U6.12 (+IN_C), U11.3 (+IN_A), U11.12 (+IN_C), U12.3 (+IN_A), U12.12 (+IN_C), U13.3 (+IN_A), U13.12 (+IN_C)
unnamed: C45.1, U5.36 (REGCAP), U5.39 (REGCAP)
unnamed: D2.2 (A), R7.2
unnamed: D3.2 (A), R8.2
unnamed: D1.A, J1.1
unnamed: L1.3, U1.5 (D)
unnamed: C2.2, R3.2, U1.3 (FB)
unnamed: L1.1, U1.1 (SW)
unnamed: C5.2, U2.4 (BYP)
unnamed: R4.1, R5.2, U3.4 (ADJ)
unnamed: C47.1, U5.44 (REFCAPA), U5.45 (REFCAPB)
unnamed: C46.1, U5.42 (REFIN/REFOUT)
unnamed: R25.1, R26.2, U6.5 (+IN_B)
unnamed: R30.1, R31.2, U6.14 (+IN_D)
unnamed: R35.1, R36.2, U11.5 (+IN_B)
unnamed: R33.1, R34.2, U11.14 (+IN_D)
unnamed: R45.1, R46.2, U12.5 (+IN_B)
unnamed: R43.1, R44.2, U12.14 (+IN_D)
unnamed: R55.1, R56.2, U13.5 (+IN_B)
RESET: J7.1, U5.11 (RESET)
S1: C10.2, J3.2, R22.2, U6.2 (-IN_A)
S2: C12.2, J3.3, R27.2, U6.11 (-IN_C)
S3: C14.2, J3.4, R37.2, U11.2 (-IN_A)
S4: C13.2, J3.5, R32.2, U11.11 (-IN_C)
S5: C16.2, J3.6, R47.2, U12.2 (-IN_A)
S6: C15.2, J3.7, R42.2, U12.11 (-IN_C)
S7: C18.2, J3.8, R57.2, U13.2 (-IN_A)
S8: J3.9, J5.3
SPI_CS: J7.4, U5.13 (~CS)
SPI_MISO: J7.5, U5.24 (DB7/DOUT_A)
SPI_SCK: J7.3, U5.12 (~RD/SCLK)
S_sac: C8.2, J5.2, R10.2, U13.11 (-IN_C)
V_sac: C8.1, R10.1, R25.2, R30.2, R33.2, R35.2, R43.2, R45.2, R55.2, U13.10 (OUT_C)
Vdrive: J7.7, U5.6 (~PAR/SER/BYTE_SEL), U5.7 (~STBY), U5.23 (Vdrive), U5.34 (REF_SELECT)
Vout1: R24.2, U5.49 (V1), U6.7 (OUT_B)
Vout2: R29.2, U5.51 (V2), U6.16 (OUT_D)
Vout3: R39.2, U5.53 (V3), U11.7 (OUT_B)
Vout4: R38.2, U5.55 (V4), U11.16 (OUT_D)
Vout5: R49.2, U5.57 (V5), U12.7 (OUT_B)
Vout6: R48.2, U5.59 (V6), U12.16 (OUT_D)
Vout7: R59.2, U5.61 (V7), U13.7 (OUT_B)
in-_b1: R23.1, R24.1, U6.6 (-IN_B)
in-_b2: R39.1, R40.1, U11.6 (-IN_B)
in-_b3: R49.1, R50.1, U12.6 (-IN_B)
in-_b4: R59.1, R60.1, U13.6 (-IN_B)
in-_c1: R28.1, R29.1, U6.15 (-IN_D)
in-_c2: R38.1, R41.1, U11.15 (-IN_D)
in-_c3: R48.1, R51.1, U12.15 (-IN_D)
out_a1: C10.1, R22.1, R23.2, U6.1 (OUT_A)
out_a2: C14.1, R37.1, R40.2, U11.1 (OUT_A)
out_a3: C16.1, R47.1, R50.2, U12.1 (OUT_A)
out_a4: C18.1, R57.1, R60.2, U13.1 (OUT_A)
out_b1: C12.1, R27.1, R28.2, U6.10 (OUT_C)
out_b2: C13.1, R32.1, R41.2, U11.10 (OUT_C)
out_b3: C15.1, R42.1, R51.2, U12.10 (OUT_C)
